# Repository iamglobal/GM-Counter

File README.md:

# GM-Counter
This is my first project of my own. GM-Counter is a long-term pre-graduation project for SPŠ na Proseku for the year 2025.

## Sources: 
- [SBM-20 data](https://www.gstube.com/data/2398/)
- [GM tubes comparison](https://iot-devices.com.ua/en/comparison-of-geiger-muller-tubes-sbm20-j305-and-lnd712/)
- [GM counter project](https://hackaday.io/project/183103-ggreg20v3-ionizing-radiation-detector)
- [Twin tube GM counter project](https://www.giangrandi.org/electronics/twin-tube-geiger/twin-tube-geiger.shtml)
- [GM Tubes info - CPM to uSv etc.](https://sites.google.com/site/diygeigercounter/technical/gm-tubes-supported)

## Components: 
- [GM kit with M4011 tube (first testing etc.)](https://www.aliexpress.com/item/1005005983829775.html?spm=a2g0o.productlist.main.11.7121URtvURtvMy&algo_pvid=5fe86294-a9dc-4aaa-9061-8c6e2802d0c6&algo_exp_id=5fe86294-a9dc-4aaa-9061-8c6e2802d0c6-4&pdp_npi=4%40dis%21USD%2161.17%2127.52%21%21%21442.65%21199.19%21%402103891017381561898268692e9547%2112000036629548116%21sea%21CZ%212394786101%21X&curPageLogUid=Xi7JYKipq4hK&utparam-url=scene%3Asearch%7Cquery_from%3A)
- [SBM-20 GM tube](https://www.ebay.com/itm/280865770387)
- [GM TUBE HOLDER PART](https://cz.mouser.com/ProductDetail/Littelfuse/01020071Z?qs=hgmQaE9nnAzCBYDQcIezzw%3D%3D&mgh=1&utm_id=20241108148&gad_source=1&gclid=CjwKCAiAqfe8BhBwEiwAsne6gTlMIWkbKxuYqfzqJkvFZII9L_CmRXRxLEZJgrcLe5JKkTACVJxdnRoC8PwQAvD_BwE)
- Arduino Nano
- 0,96 inch OLED display

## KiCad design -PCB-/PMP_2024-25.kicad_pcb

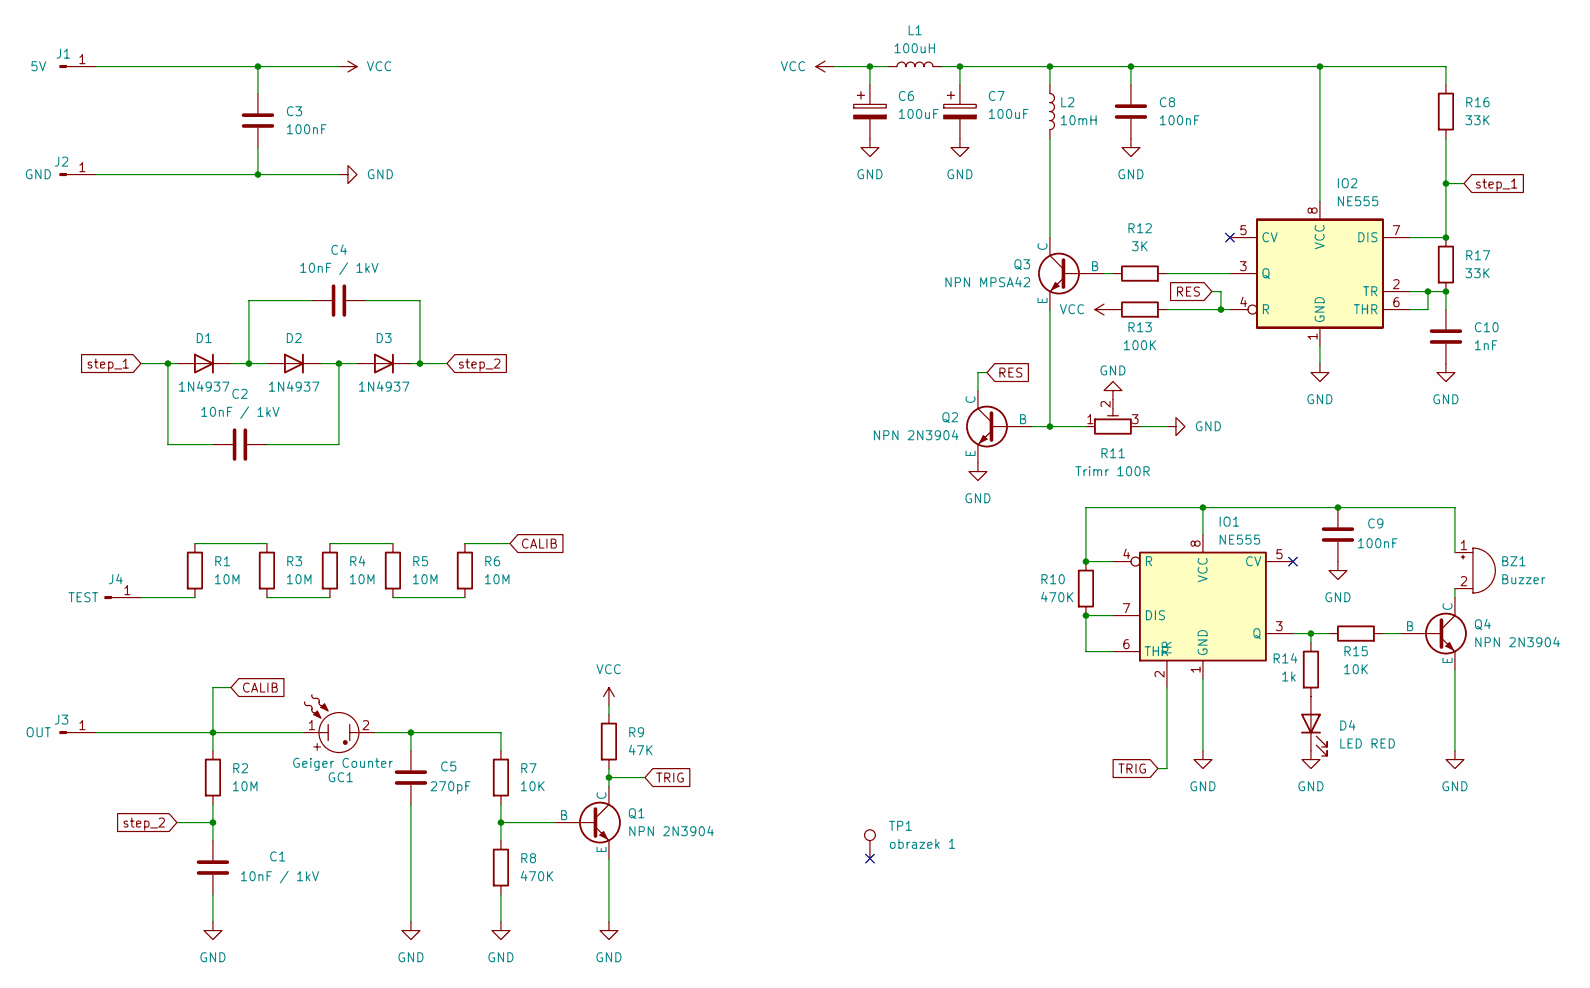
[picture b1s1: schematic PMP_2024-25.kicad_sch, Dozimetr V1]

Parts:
BZ1: Buzzer; Buzzer_15x7.5RM7.6
C1, C2, C4: 10nF / 1kV; C_Disc_D4.3mm_W1.9mm_P5.00mm
C3, C8, C9: 100nF; C_Disc_D4.3mm_W1.9mm_P5.00mm
C5: 270pF; C_Disc_D4.3mm_W1.9mm_P5.00mm
C6, C7: 100uF; CP_Radial_D6.3mm_P2.50mm
C10: 1nF; C_Disc_D4.3mm_W1.9mm_P5.00mm
D1, D2, D3: 1N4937; D_A-405_P10.16mm_Horizontal
D4: LED RED; LED_D5.0mm
GC1: Geiger Counter; GeigerTube Holder v3 (final)
IO1, IO2: NE555; DIP-8_W7.62mm_Socket_LongPads
J1: 5V; PinHeader_1x01_P1.00mm_Vertical
J2: GND; PinHeader_1x01_P1.00mm_Vertical
J3: OUT; PinHeader_1x01_P1.00mm_Vertical
J4: TEST; PinHeader_1x01_P1.00mm_Vertical
L1: 100uH; L_Axial_L7.0mm_D3.3mm_P12.70mm_Horizontal_Fastron_MICC
L2: 10mH; L_Radial_D10.0mm_P5.00mm_Fastron_07M
Q1, Q2, Q4: NPN 2N3904; TO-92
Q3: NPN MPSA42; TO-92
R1, R2, R3, R4, R5, R6: 10M; R_Axial_DIN0207_L6.3mm_D2.5mm_P10.16mm_Horizontal
R7, R15: 10K; R_Axial_DIN0207_L6.3mm_D2.5mm_P10.16mm_Horizontal
R8, R10: 470K; R_Axial_DIN0207_L6.3mm_D2.5mm_P10.16mm_Horizontal
R9: 47K; R_Axial_DIN0207_L6.3mm_D2.5mm_P10.16mm_Horizontal
R11: Trimr 100R; Potentiometer_Bourns_3296W_Vertical
R12: 3K; R_Axial_DIN0207_L6.3mm_D2.5mm_P10.16mm_Horizontal
R13: 100K; R_Axial_DIN0207_L6.3mm_D2.5mm_P10.16mm_Horizontal
R14: 1k; R_Axial_DIN0207_L6.3mm_D2.5mm_P10.16mm_Horizontal
R16, R17: 33K; R_Axial_DIN0207_L6.3mm_D2.5mm_P10.16mm_Horizontal
TP1: obrazek 1; obrazek1

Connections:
CALIB: GC1.1, J3.1, R2.1, R6.1
GND: C1.1, C3.2, C5.1, C6.2, C7.2, C8.2, C9.1, C10.2, D4.1 (K), IO1.1 (GND), IO2.1 (GND), J2.1, Q1.3 (E), Q2.3 (E), Q4.3 (E), R8.2, R11.2, R11.3; also elsewhere on the board
unnamed: BZ1.1 (+), C9.2, IO1.4 (R), IO1.8 (VCC), R10.1
unnamed: BZ1.2 (-), Q4.1 (C)
unnamed: C5.2, GC1.2, R7.1
unnamed: C4.2, D1.1 (K), D2.2 (A)
unnamed: C2.1, D2.1 (K), D3.2 (A)
unnamed: D4.2 (A), R14.2
unnamed: IO1.6 (THR), IO1.7 (DIS), R10.2
unnamed: IO1.3 (Q), R14.1, R15.1
unnamed: IO2.3 (Q), R12.2
unnamed: C10.1, IO2.2 (TR), IO2.6 (THR), R17.2
unnamed: C7.1, C8.1, IO2.8 (VCC), L1.2, L2.1, R16.1
unnamed: J4.1, R1.2
unnamed: Q1.2 (B), R7.2, R8.1
unnamed: Q2.2 (B), Q3.3 (E), R11.1
unnamed: Q3.2 (B), R12.1
unnamed: L2.2, Q3.1 (C)
unnamed: Q4.2 (B), R15.2
unnamed: R1.1, R3.1
unnamed: R3.2, R4.2
unnamed: R4.1, R5.1
unnamed: R5.2, R6.2
RES: IO2.4 (R), Q2.1 (C), R13.2
TRIG: IO1.2 (TR), Q1.1 (C), R9.2
VCC: C3.1, C6.1, J1.1, L1.1, R9.1, R13.1
step_1: C2.2, D1.2 (A), IO2.7 (DIS), R16.2, R17.1
step_2: C1.2, C4.1, D3.1 (K), R2.2

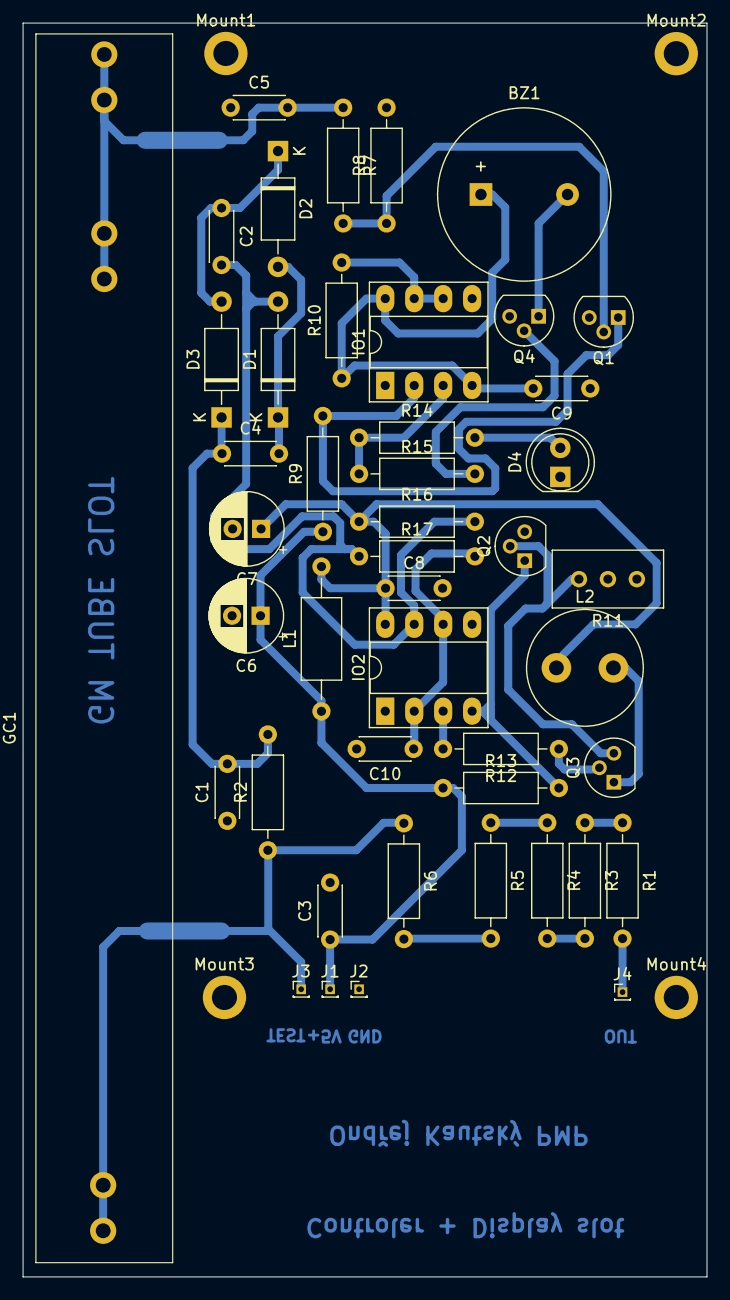
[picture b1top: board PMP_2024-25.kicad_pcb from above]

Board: 2 copper layers, 60.0 x 110.0 mm, 50 parts (1 on the bottom side), 28 nets.

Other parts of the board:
Mount1, Mount2, Mount3, Mount4: MountingHole_2.2mm_M2_DIN965_Pad

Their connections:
GND: Mount1.1, Mount2.1, Mount3.1, Mount4.1; also elsewhere on the board

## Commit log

2025-01-27 first push
    -
2025-01-27 first push (CODE FOLDER)
    mainly display settings (tests etc.)
2025-01-27 Update README.md
    Sources added
2025-01-27 Update README.md
    sources edit
2025-01-27 gitignore edit
    changed gitignore to .gitignore
2025-01-27 backups deleted
    -
2025-01-27 gitignore test
    -
2025-01-27 folders edit
    creating new folder for 3D
2025-01-29 Update README.md
    added few sources
2025-01-29 Update README.md
    added better formating
2025-01-29 Update README.md
    Added components to README
2025-01-29 Update README.md
    deleted hyperlink test.
2025-01-31 Documentation folder added
    just an dummy txt
2025-02-01 Update README.md
    added more resources
2025-02-01 Update README.md
    added holder for gm tube
2025-02-24 some edits
    excel added too
2025-02-27 excel added
2025-02-27 schematic update
    odebrany chyby, pridany krizky apod
2025-02-27 update excel
2025-03-01 excel updated
    added codes (TME)
2025-03-01 last update
    soucastky ordered
2025-03-07 update exccelll
    added + and -
2025-03-07 PCB update
    V2
2025-03-07 more changes
2025-03-07 PCB pre-final
    full pcb design V2 - will add picture on the pcb soon
2025-03-07 added image on PCB
    PDF prints added too
2025-03-09 deleted dummy file
    -
2025-03-09 Presentation added
    Presentation for Praxe with Knop
2025-03-09 Research from ipad (PDF)
    last update 8.3.
    geiger tubes, first design ideas, some important info
2025-03-09 schematic from kicad
    exported to pdf
2025-03-09 EDITS ON CHEMATIC AND PCB
    renamed pins and changed positions
2025-03-09 edits before submititng
2025-03-09 DOCS UPDATE
    added pngs of first versions of PCB
    edit in original document about the project
2025-04-15 edits on pcb, design etc.
    box model soon, tommorow creating pcb v2
2025-04-15 text edits
    +export
2025-04-20 presentation update
